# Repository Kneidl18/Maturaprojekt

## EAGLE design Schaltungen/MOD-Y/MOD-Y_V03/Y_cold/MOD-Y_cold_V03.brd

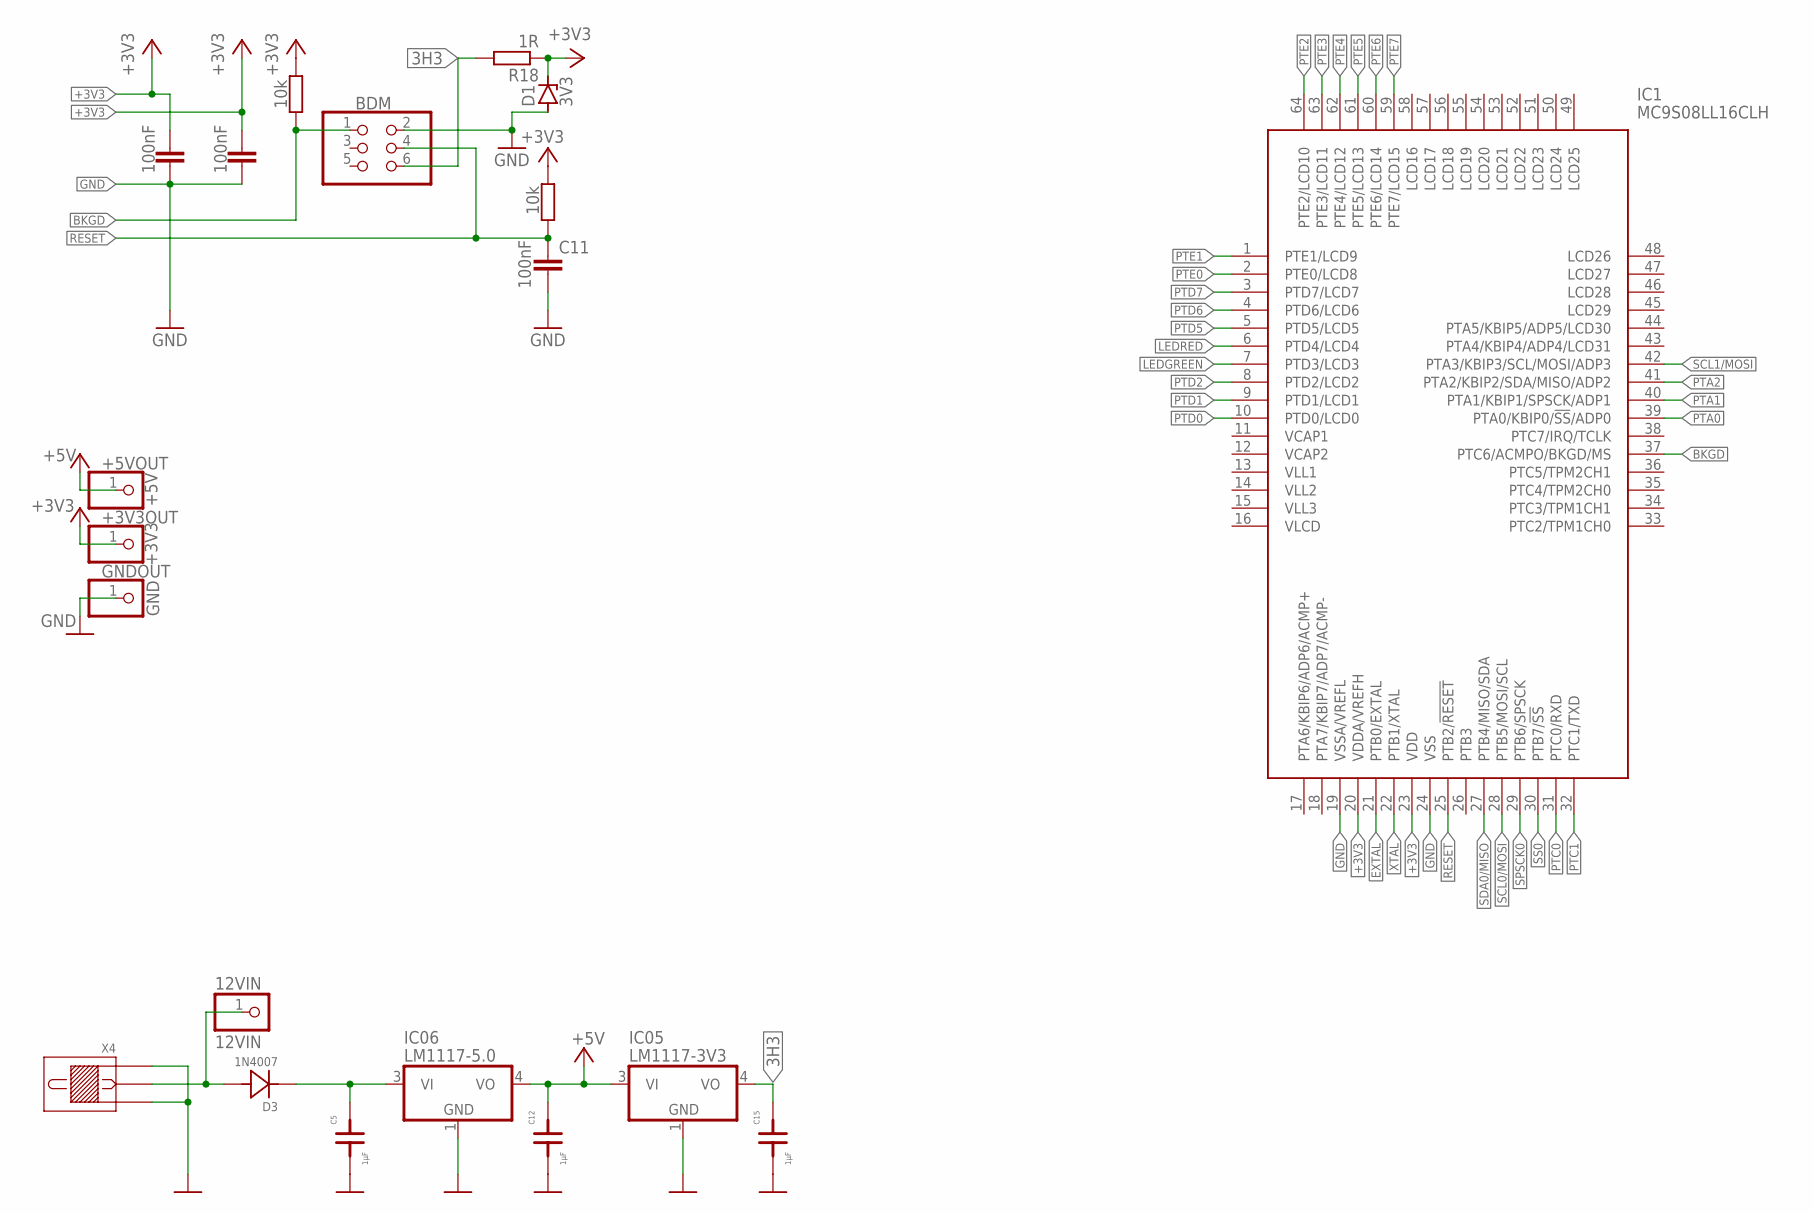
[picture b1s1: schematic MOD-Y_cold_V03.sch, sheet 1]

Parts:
12VIN: 12VIN; 1X01
+3V3OUT: +3V3; 1X01
+5VOUT: +5V; 1X01
BDM: PINHD-2X3; 2X03
C5, C12, C15: 1µF; 0805F
C9, C10, C11: 100nF; C0805
D1: 3V3; SOD80C
D3: 1N4007; MELF_B
GNDOUT: GND; 1X01
IC1: MC9S08LL16CLH; QFP50P1200X1200X160-64N
IC05: LM1117-3V3; DPAK
IC06: LM1117-5.0; DPAK
R16, R17: 10k; R0805
R18: 1R; R0805
X4: SPP

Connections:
3H3: BDM.6, C15.2, IC05.4 (VO), R18.2
+3V3: +3V3OUT.1, C9.1, C10.1, D1.C, IC1.20 (VDDA/VREFH), IC1.23 (VDD), R16.2, R17.2, R18.1; also elsewhere on the board
+5V: +5VOUT.1, C12.2, IC05.3 (VI), IC06.4 (VO); also elsewhere on the board
BKGD: BDM.1, IC1.37 (PTC6/ACMPO/BKGD/MS), R16.1
EXTAL: IC1.21 (PTB0/EXTAL); also elsewhere on the board
GND: BDM.2, C5.1, C9.2, C10.2, C11.2, C12.1, C15.1, D1.A, GNDOUT.1, IC1.19 (VSSA/VREFL), IC1.24 (VSS), IC05.1 (GND), IC06.1 (GND), X4.1, X4.3; also elsewhere on the board
LEDGREEN: IC1.7 (PTD3/LCD3); also elsewhere on the board
LEDRED: IC1.6 (PTD4/LCD4); also elsewhere on the board
unnamed: C5.2, D3.K, IC06.3 (VI)
unnamed: 12VIN.1, D3.A, X4.2
PTA0: IC1.39 (PTA0/KBIP0/!SS!/ADP0); also elsewhere on the board
PTA1: IC1.40 (PTA1/KBIP1/SPSCK/ADP1); also elsewhere on the board
PTA2: IC1.41 (PTA2/KBIP2/SDA/MISO/ADP2); also elsewhere on the board
PTC0: IC1.31 (PTC0/RXD); also elsewhere on the board
PTC1: IC1.32 (PTC1/TXD); also elsewhere on the board
PTD0: IC1.10 (PTD0/LCD0)
PTD1: IC1.9 (PTD1/LCD1)
PTD2: IC1.8 (PTD2/LCD2)
PTD5: IC1.5 (PTD5/LCD5); also elsewhere on the board
PTD6: IC1.4 (PTD6/LCD6); also elsewhere on the board
PTD7: IC1.3 (PTD7/LCD7); also elsewhere on the board
PTE0: IC1.2 (PTE0/LCD8); also elsewhere on the board
PTE1: IC1.1 (PTE1/LCD9); also elsewhere on the board
PTE2: IC1.64 (PTE2/LCD10); also elsewhere on the board
PTE3: IC1.63 (PTE3/LCD11); also elsewhere on the board
PTE4: IC1.62 (PTE4/LCD12); also elsewhere on the board
PTE5: IC1.61 (PTE5/LCD13); also elsewhere on the board
PTE6: IC1.60 (PTE6/LCD14)
PTE7: IC1.59 (PTE7/LCD15)
RESET: BDM.4, C11.1, IC1.25 (PTB2/!RESET), R17.1
SCL0/MOSI: IC1.28 (PTB5/MOSI/SCL); also elsewhere on the board
SCL1/MOSI: IC1.42 (PTA3/KBIP3/SCL/MOSI/ADP3)
SDA0/MISO: IC1.27 (PTB4/MISO/SDA); also elsewhere on the board
SPSCK0: IC1.29 (PTB6/SPSCK); also elsewhere on the board
SS0: IC1.30 (PTB7/!SS); also elsewhere on the board
XTAL: IC1.22 (PTB1/XTAL); also elsewhere on the board

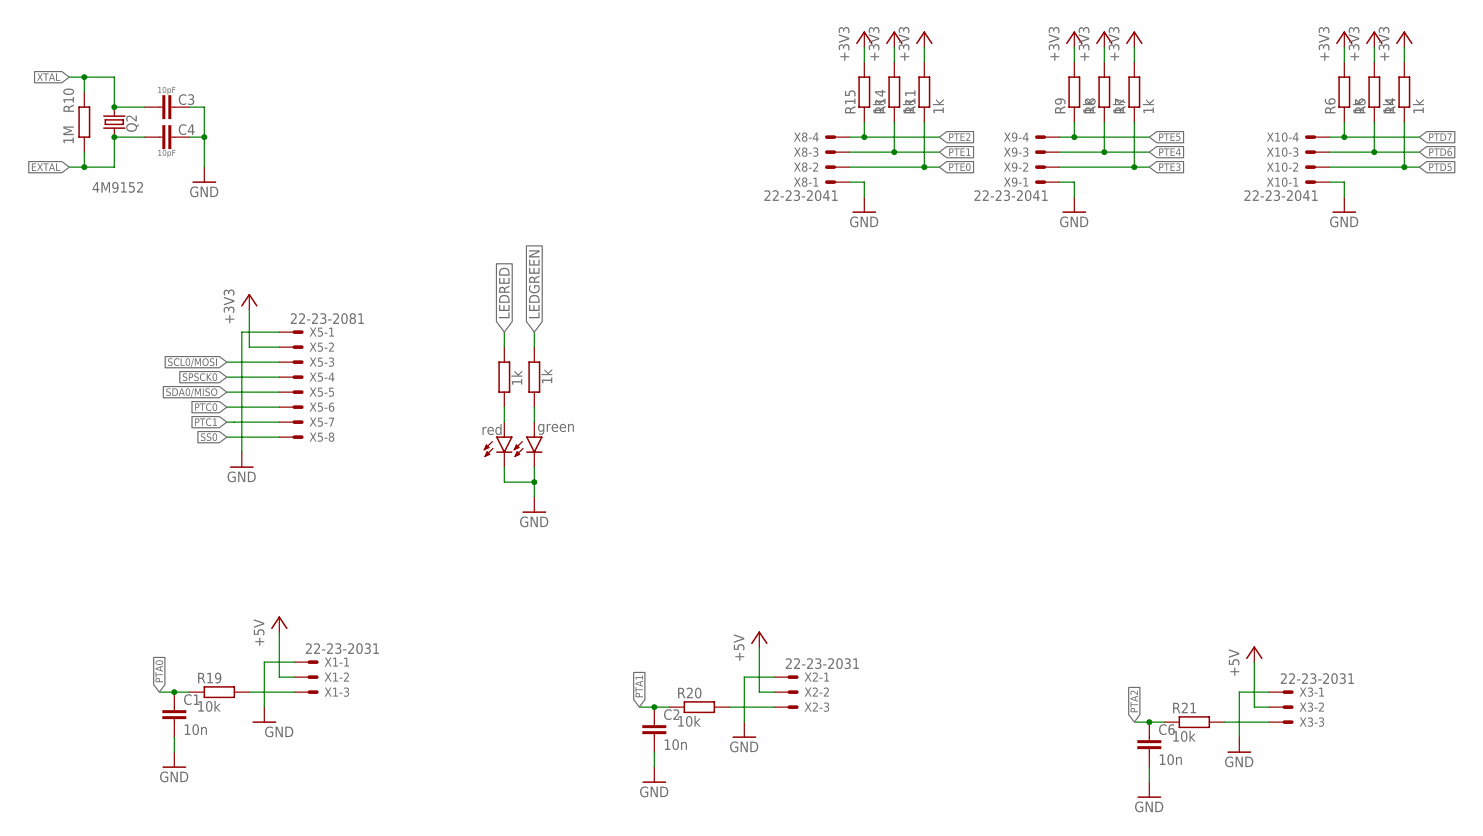
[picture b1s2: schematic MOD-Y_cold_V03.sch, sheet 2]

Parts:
C1, C2, C6: 10n; C0805
C3, C4: 10pF; C0805
LED1: green; CHIP-LED0805
LED2: red; CHIP-LED0805
Q2: 4M9152; HC49UP
R4, R5, R6, R7, R8, R9, R11, R12, R13, R14, R15: 1k; R0805
R10: 1M; R0805
R19, R20, R21: 10k; R0805
X1, X2, X3: 22-23-2031
X5: 22-23-2081
X8, X9, X10: 22-23-2041

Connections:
+3V3: R4.2, R5.2, R6.2, R7.2, R8.2, R9.2, R11.2, R14.2, R15.2, X5.2; also elsewhere on the board
+5V: X1.2, X2.2, X3.2; also elsewhere on the board
EXTAL: C4.1, Q2.1, R10.1; also elsewhere on the board
GND: C1.2, C2.2, C3.2, C4.2, C6.2, LED1.C, LED2.C, X1.1, X2.1, X3.1, X5.1, X8.1, X9.1, X10.1; also elsewhere on the board
LEDGREEN: R13.2; also elsewhere on the board
LEDRED: R12.2; also elsewhere on the board
unnamed: R21.2, X3.3
unnamed: R19.2, X1.3
unnamed: R20.2, X2.3
unnamed: LED2.A, R12.1
unnamed: LED1.A, R13.1
PTA0: C1.1, R19.1; also elsewhere on the board
PTA1: C2.1, R20.1; also elsewhere on the board
PTA2: C6.1, R21.1; also elsewhere on the board
PTC0: X5.6; also elsewhere on the board
PTC1: X5.7; also elsewhere on the board
PTD5: R4.1, X10.2; also elsewhere on the board
PTD6: R5.1, X10.3; also elsewhere on the board
PTD7: R6.1, X10.4; also elsewhere on the board
PTE0: R11.1, X8.2; also elsewhere on the board
PTE1: R14.1, X8.3; also elsewhere on the board
PTE2: R15.1, X8.4; also elsewhere on the board
PTE3: R7.1, X9.2; also elsewhere on the board
PTE4: R8.1, X9.3; also elsewhere on the board
PTE5: R9.1, X9.4; also elsewhere on the board
SCL0/MOSI: X5.3; also elsewhere on the board
SDA0/MISO: X5.5; also elsewhere on the board
SPSCK0: X5.4; also elsewhere on the board
SS0: X5.8; also elsewhere on the board
XTAL: C3.1, Q2.2, R10.2; also elsewhere on the board

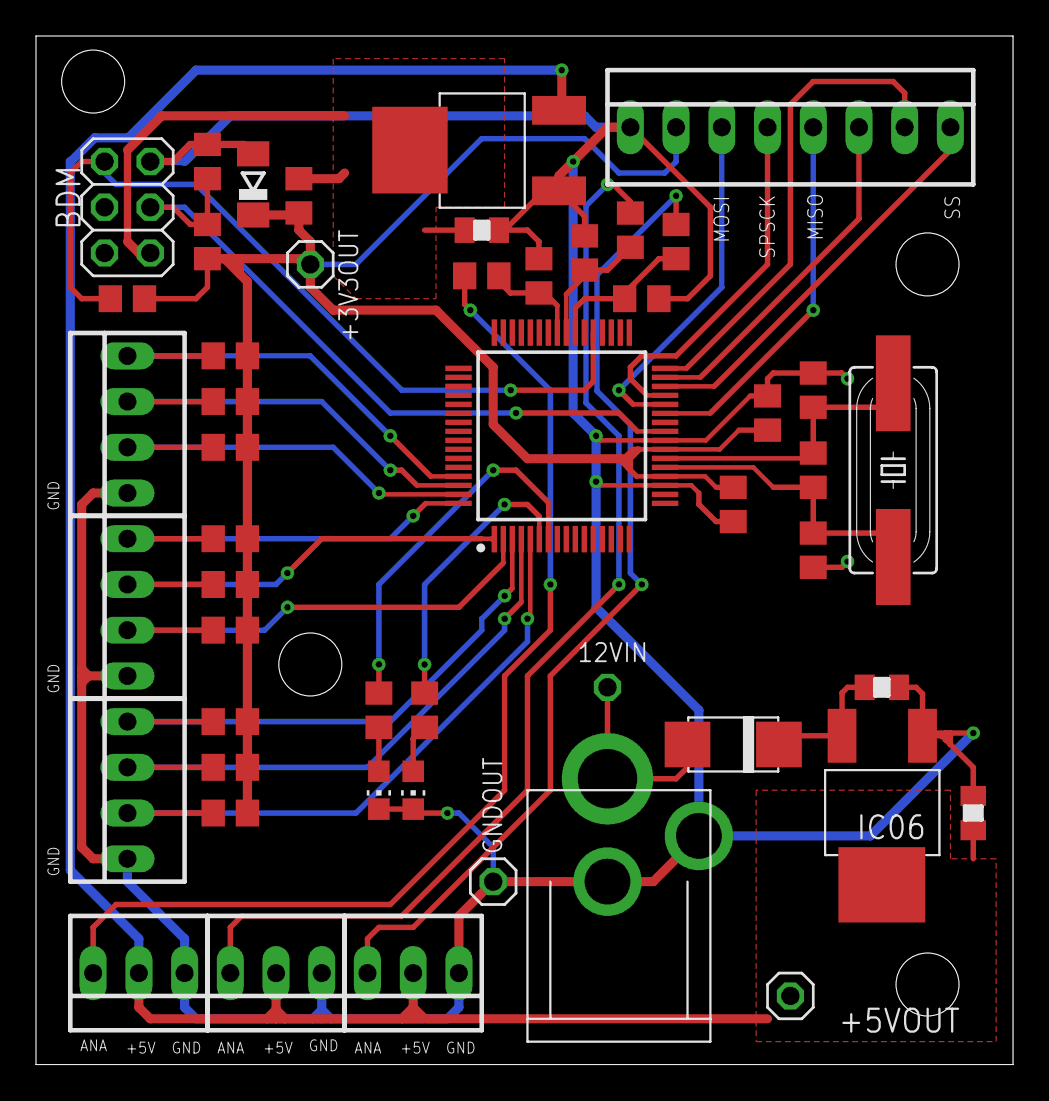
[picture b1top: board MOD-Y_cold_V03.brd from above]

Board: 2 copper layers, 54.3 x 57.1 mm, 50 parts (1 on the bottom side), 35 nets.

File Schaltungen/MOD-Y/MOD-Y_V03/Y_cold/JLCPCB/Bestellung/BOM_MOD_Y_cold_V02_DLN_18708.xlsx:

Comment | Designator | Footprint | LCSC Part #（optional）
10pF | C3, C4 | 0805_C | C1785
1µF | C5, C12, C15 | 0805_C | C28323
10nF | C1, C2, C6 | 0805_C | C1710
100nF | C9, C10, C11 | 0805_C | C49678
1R | R18 | 0805_R | C25271
1k | R4, R5, R6, R7, R8, R9, R11, R12, R13, R14, R15 | 0805_R | C17513
10k | R16, R17, R19, R20, R21 | 0805_R | C17414
1M | R10 | 0805_R | C228604

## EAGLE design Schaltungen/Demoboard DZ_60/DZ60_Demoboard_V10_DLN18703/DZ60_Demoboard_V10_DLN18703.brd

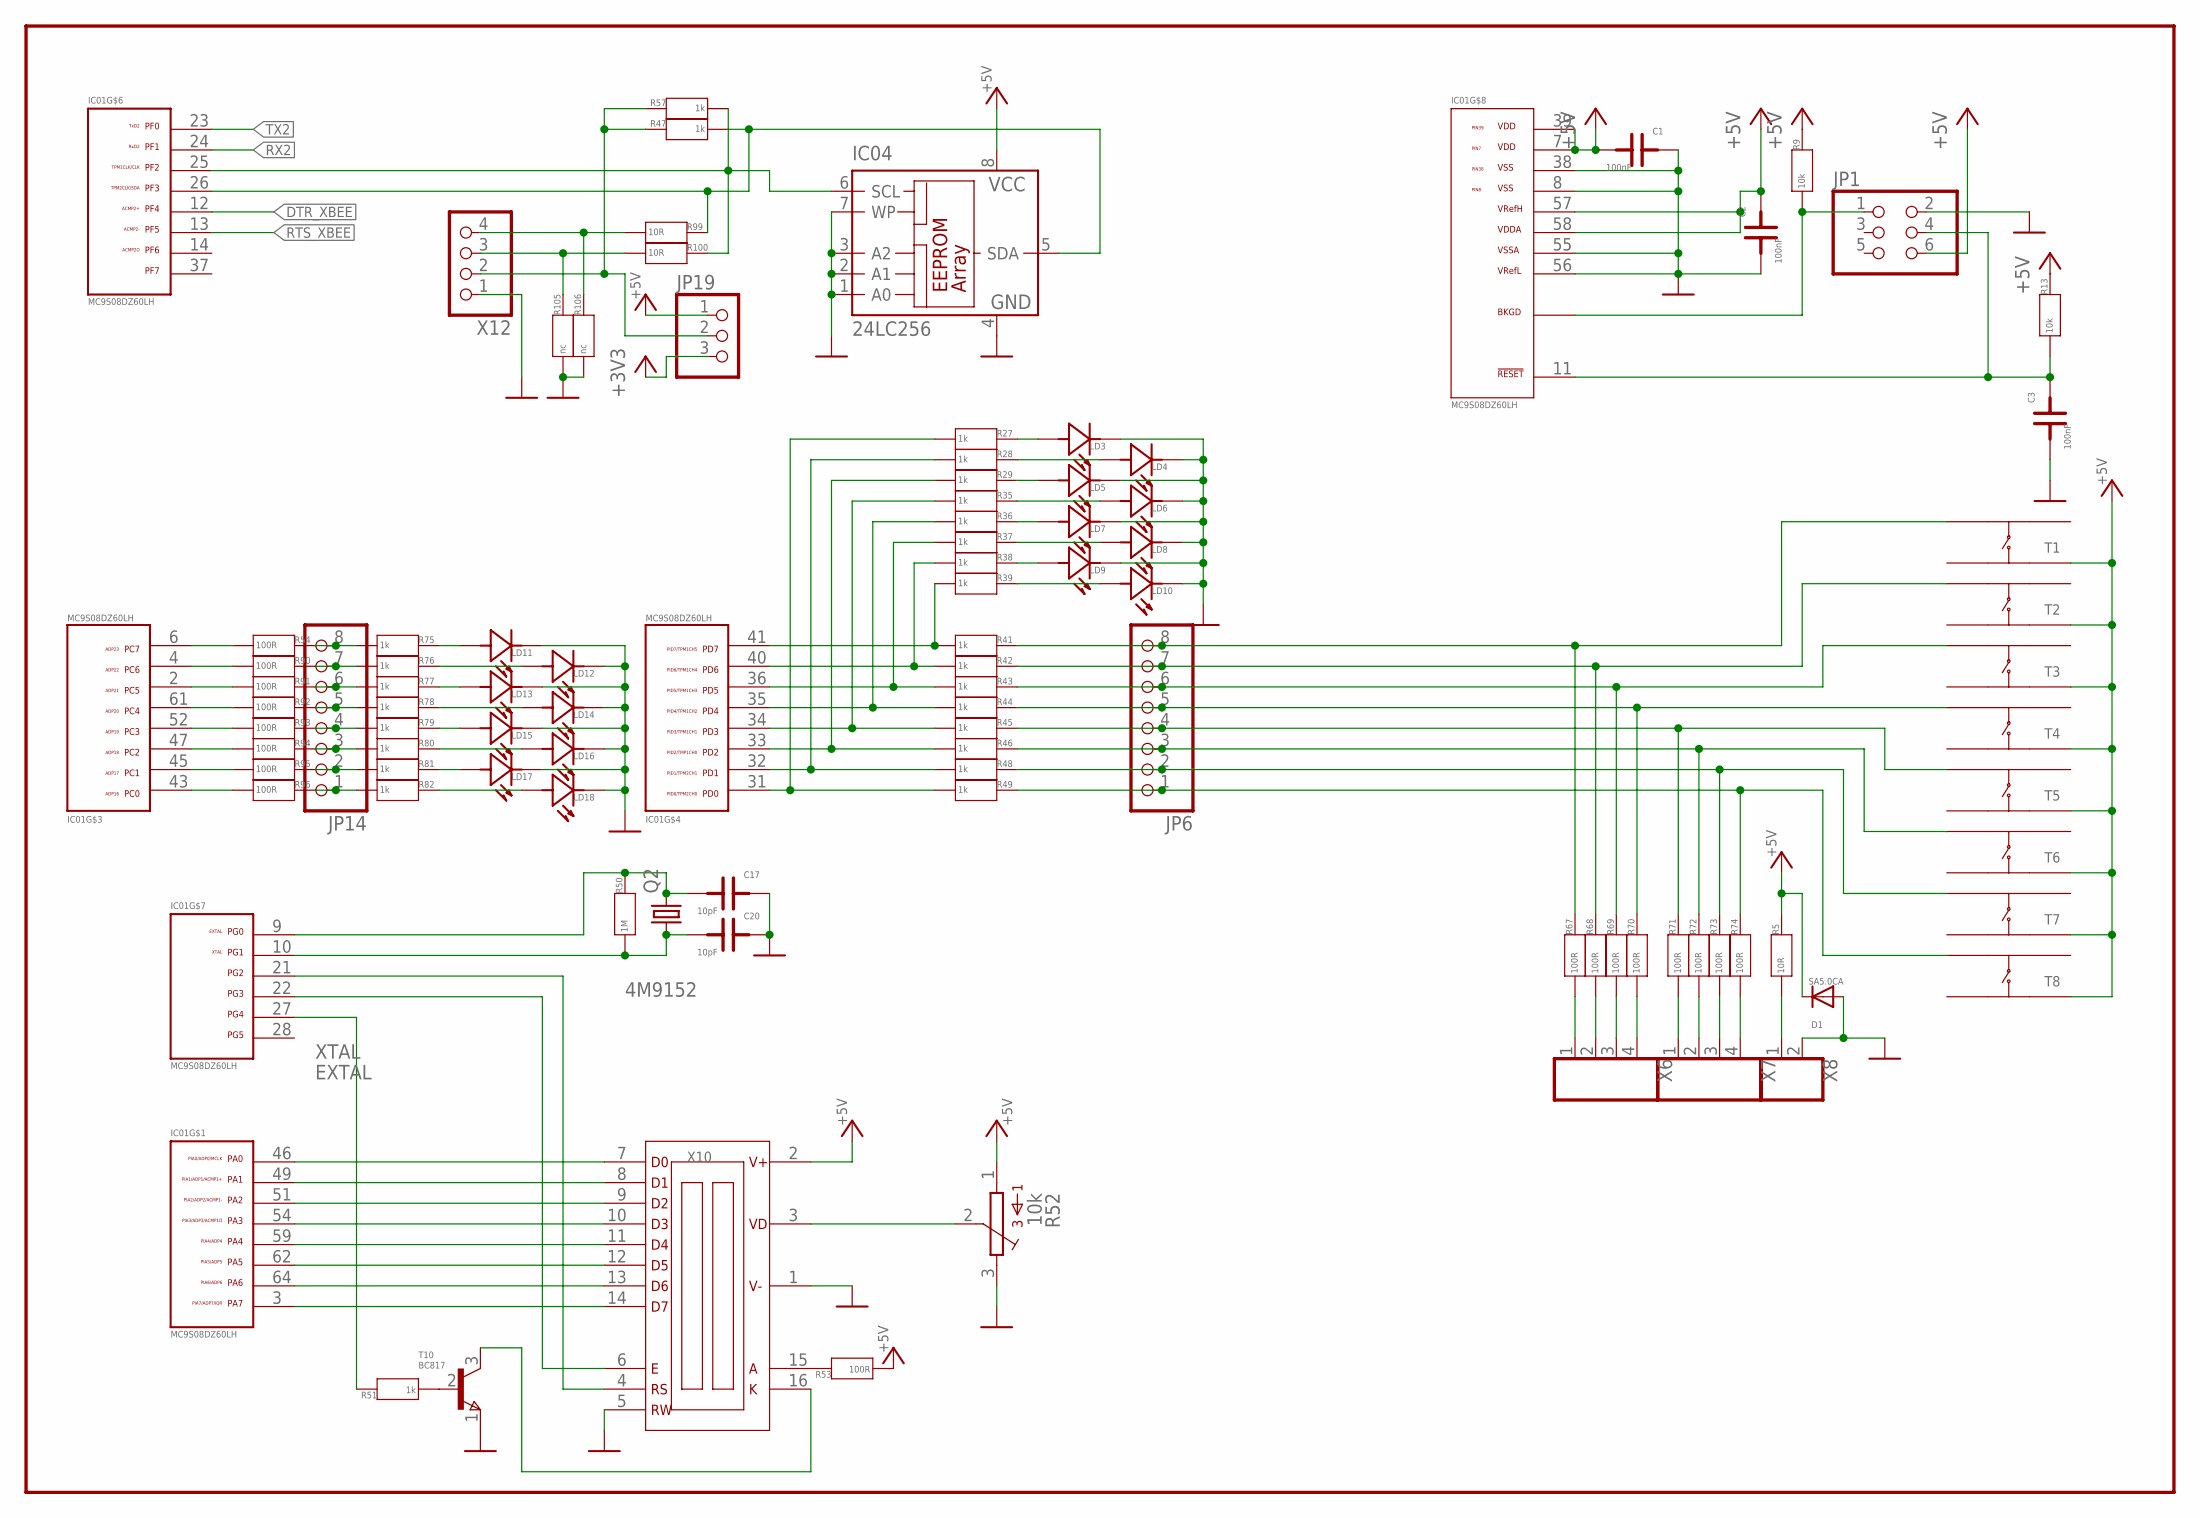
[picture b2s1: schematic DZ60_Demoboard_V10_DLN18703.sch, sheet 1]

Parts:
C1, C2, C3: 100nF; 0805F
C17, C20: 10pF; 0805F
D1: SA5.0CA; SMB
IC01: MC9S08DZ60LH; LQFP64
IC04: 24LC256; SO-08M
JP1: PINHD-2X3; 2X03
JP6, JP14: PINHD-1X8; 1X08
JP19: PINHD-1X3; 1X03
LD3, LD4, LD5, LD6, LD7, LD8, LD9, LD10, LD11, LD12, LD13, LD14, LD15, LD16, LD17, LD18: LEDSMD; 0805LED
Q2: 4M9152; HC49UP
R5, R99, R100: 10R; 0805
R9, R13: 10k; 0805
R27, R28, R29, R35, R36, R37, R38, R39, R41, R42, R43, R44, R45, R46, R47, R48, R49, R51, R57, R75, R76, R77, R78, R79, R80, R81, R82: 1k; 0805
R50: 1M; 0805
R52: 10k; S63X
R53, R54, R67, R68, R69, R70, R71, R72, R73, R74, R90, R91, R92, R93, R94, R95, R96: 100R; 0805
R105, R106: nc; 0805
T1, T2, T3, T4, T5, T6, T7, T8: TASTERTHT; TASTE_THT
T10: BC817; SOT-23
X6, X7: KLEMME4
X8: KLEMME2
X10: FDCC1602G
X12: MX254_4; MX4

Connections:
+3V3: JP19.3; also elsewhere on the board
+5V: C1.1, C2.2, D1.C, IC01.7 (VDD_PIN7), IC01.39 (VDD_PIN39), IC01.57 (VREFH), IC01.58 (VDDA), IC04.8 (VCC), JP1.6, JP19.1, R5.2, R9.2, R13.2, R52.1, R53.1, T1.A1, T2.A1, T3.A1, T4.A1, T5.A1, T6.A1, T7.A1, T8.A1, X10.2 (V+); also elsewhere on the board
BKGD: IC01.42 (BKGD), JP1.1, R9.1
D0: IC01.46 (PA0), X10.7 (D0)
D1: IC01.49 (PA1), X10.8 (D1)
D2: IC01.51 (PA2), X10.9 (D2)
D3: IC01.54 (PA3), X10.10 (D3)
D4: IC01.59 (PA4), X10.11 (D4)
D5: IC01.62 (PA5), X10.12 (D5)
D6: IC01.64 (PA6), X10.13 (D6)
D7: IC01.3 (PA7), X10.14 (D7)
DTR_XBEE: IC01.12 (PF4); also elsewhere on the board
E: IC01.22 (PG3), X10.6 (E)
EXTAL: C20.1, IC01.10 (PG1), Q2.1, R50.1
GND: C1.2, C2.1, C3.1, C17.2, C20.2, D1.A, IC01.8 (VSS_PIN8), IC01.38 (VSS_PIN38), IC01.55 (VSSA), IC01.56 (VREFL), IC04.1 (A0), IC04.2 (A1), IC04.3 (A2), IC04.4 (GND), IC04.7 (WP), JP1.2, LD3.K (1), LD4.K (1), LD5.K (1), LD6.K (1), LD7.K (1), LD8.K (1), LD9.K (1), LD10.K (1), LD11.K (1), LD12.K (1), LD13.K (1), LD14.K (1), LD15.K (1), LD16.K (1), LD17.K (1), LD18.K (1), R52.3, R105.1, R106.1, T10.1 (E), X8.2, X10.1 (V-), X10.5 (RW), X12.1; also elsewhere on the board
LCD_LED1: IC01.27 (PG4), R51.2
unnamed: R53.2, X10.15 (A)
unnamed: LD11.A (2), R75.2
unnamed: LD12.A (2), R76.2
unnamed: LD3.A (2), R27.2
unnamed: LD4.A (2), R28.2
unnamed: LD5.A (2), R29.2
unnamed: LD6.A (2), R35.2
unnamed: LD7.A (2), R36.2
unnamed: LD8.A (2), R37.2
unnamed: LD9.A (2), R38.2
unnamed: LD10.A (2), R39.2
unnamed: R51.1, T10.2 (B)
unnamed: R5.1, X8.1
unnamed: R52.2, X10.3 (VD)
unnamed: T10.3 (C), X10.16 (K)
unnamed: LD13.A (2), R77.2
unnamed: LD14.A (2), R78.2
unnamed: LD15.A (2), R79.2
unnamed: LD16.A (2), R80.2
unnamed: LD17.A (2), R81.2
unnamed: LD18.A (2), R82.2
PC0: JP14.1, R82.1, R96.2
PC0M: IC01.43 (PC0), R96.1
PC1: JP14.2, R81.1, R95.2
PC1M: IC01.45 (PC1), R95.1
PC2: JP14.3, R80.1, R94.2
PC2M: IC01.47 (PC2), R94.1
PC3: JP14.4, R79.1, R93.2
PC3M: IC01.52 (PC3), R93.1
PC4: JP14.5, R78.1, R92.2
PC4M: IC01.61 (PC4), R92.1
PC5: JP14.6, R77.1, R91.2
PC5M: IC01.2 (PC5), R91.1
PC6: JP14.7, R76.1, R90.2
PC6M: IC01.4 (PC6), R90.1
PC7: JP14.8, R54.2, R75.1
PC7M: IC01.6 (PC7), R54.1
PD0: JP6.1, R49.2, R74.2, T8.B2
PD0M: IC01.31 (PD0), R27.1, R49.1
PD1: JP6.2, R48.2, R73.2, T7.B2
PD1M: IC01.32 (PD1), R28.1, R48.1
PD2: JP6.3, R46.2, R72.2, T6.B2
PD2M: IC01.33 (PD2), R29.1, R46.1
PD3: JP6.4, R45.2, R71.2, T5.B2
PD3M: IC01.34 (PD3), R35.1, R45.1
PD4: JP6.5, R44.2, R70.2, T4.B2
PD4M: IC01.35 (PD4), R36.1, R44.1
PD5: JP6.6, R43.2, R69.2, T3.B2
PD5M: IC01.36 (PD5), R37.1, R43.1
PD6: JP6.7, R42.2, R68.2, T2.B2
PD6M: IC01.40 (PD6), R38.1, R42.1
PD7: JP6.8, R41.2, R67.2, T1.B2
PD7M: IC01.41 (PD7), R39.1, R41.1
PF0A: R74.1, X7.4
PF1A: R73.1, X7.3
PF2A: R72.1, X7.2
PF3A: R71.1, X7.1
PF4A: R70.1, X6.4
PF5A: R69.1, X6.3
PF6A: R68.1, X6.2
PF7A: R67.1, X6.1
RESET: C3.2, IC01.11 (RST/), JP1.4, R13.1
RS: IC01.21 (PG2), X10.4 (RS)
RTS_XBEE: IC01.13 (PF5); also elsewhere on the board
RX2: IC01.24 (PF1); also elsewhere on the board
SCL_PF2: IC01.25 (PF2), IC04.6 (SCL), R57.1, R100.2
SCL_PIN: R100.1, R105.2, X12.3
SDA_PF3: IC01.26 (PF3), IC04.5 (SDA), R47.1, R99.2
SDA_PIN: R99.1, R106.2, X12.4
TX2: IC01.23 (PF0); also elsewhere on the board
U_I2C: JP19.2, R47.2, R57.2, X12.2
XTAL: C17.1, IC01.9 (PG0), Q2.2, R50.2

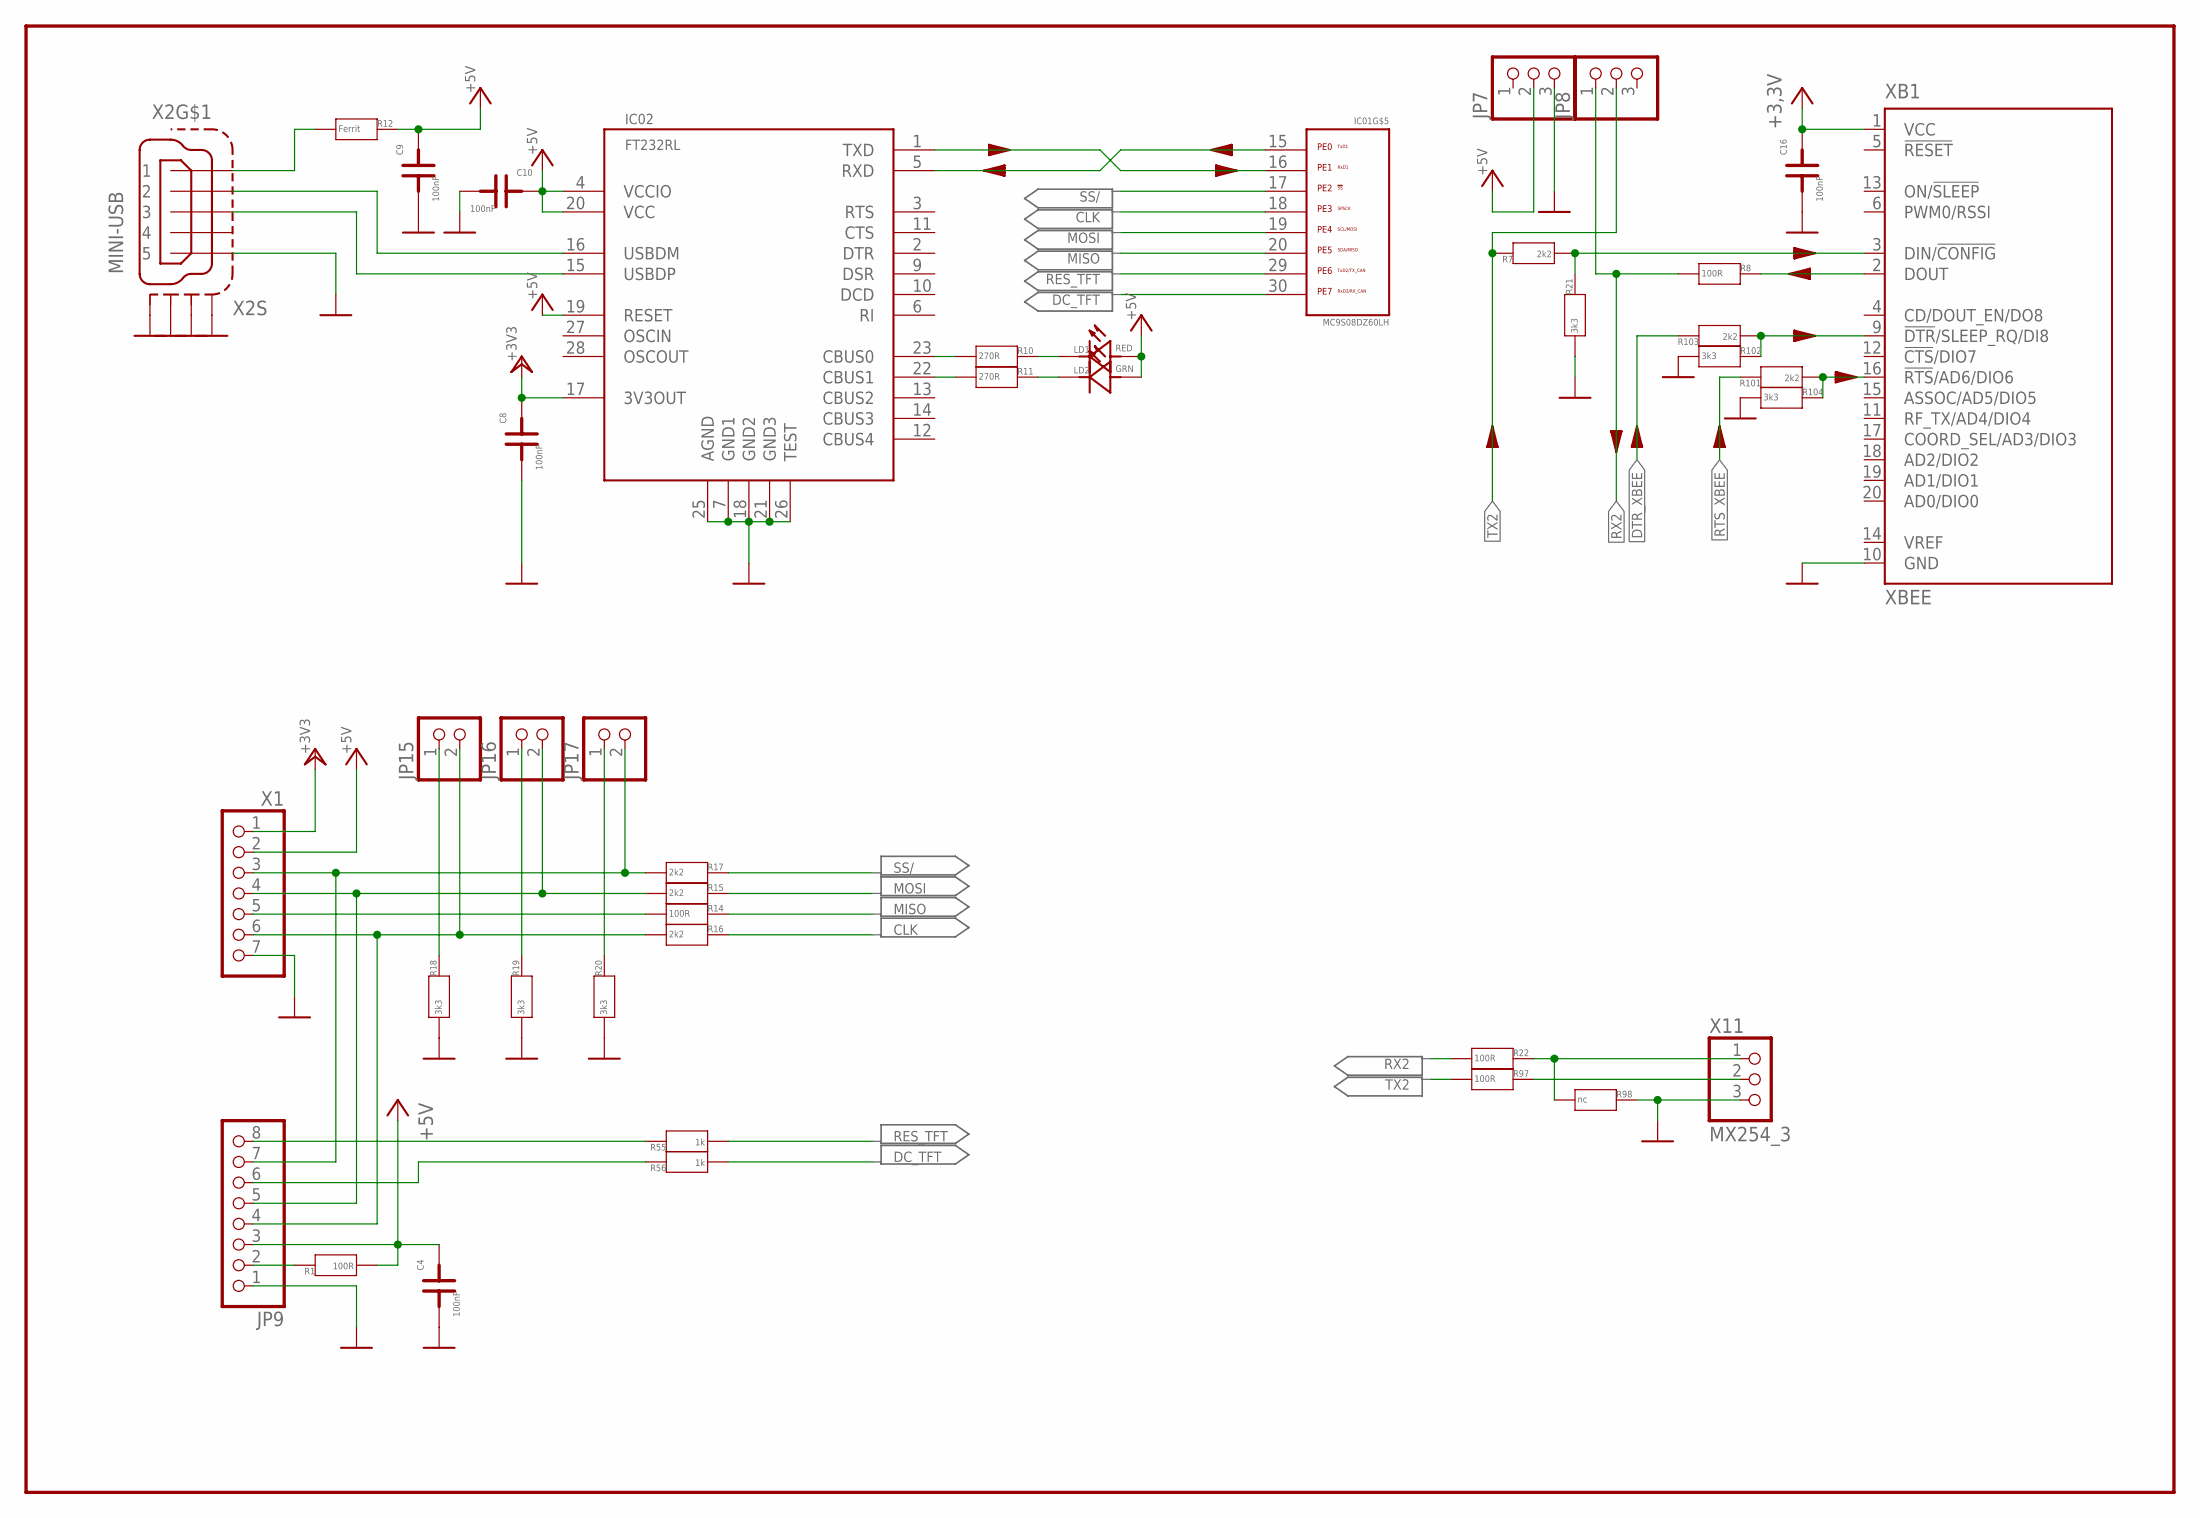
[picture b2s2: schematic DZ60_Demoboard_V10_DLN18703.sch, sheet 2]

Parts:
C4, C8, C9, C10, C16: 100nF; 0805F
IC01: MC9S08DZ60LH; LQFP64
IC02: FT232RL; SSOP28
JP7, JP8: PINHD-1X3; 1X03
JP9: PINHD-1X8; 1X08
JP15, JP16, JP17: PINHD-1X2; 1X02
LD1: RED; 0805LED
LD2: GRN; 0805LED
R1, R8, R14, R22, R97: 100R; 0805
R7, R15, R16, R17, R101, R103: 2k2; 0805
R10, R11: 270R; 0805
R12: Ferrit; 1206
R18, R19, R20, R21, R102, R104: 3k3; 0805
R55, R56: 1k; 0805
R98: nc; 0805
X1: MX254_7; MX7
X2: MINI-USB; 32005-201
X11: MX254_3; MX3
XB1: XBEE

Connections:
+3V3: C8.2, C16.2, IC02.17 (3V3OUT), X1.1, XB1.1 (VCC); also elsewhere on the board
+5V: C4.2, C9.2, C10.2, IC02.4 (VCCIO), IC02.19 (RESET), IC02.20 (VCC), JP7.2, JP9.3, LD1.A (2), LD2.A (2), R1.1, R12.2, X1.2; also elsewhere on the board
CLK: IC01.18 (PE3), R16.2
DC_TFT: IC01.30 (PE7), R56.1
DTR_XBEE: R103.2; also elsewhere on the board
GND: C4.1, C8.1, C9.1, C10.1, C16.1, IC02.7 (GND1), IC02.18 (GND2), IC02.21 (GND3), IC02.25 (AGND), IC02.26 (TEST), JP7.3, JP9.1, R18.1, R19.1, R20.1, R21.1, R98.2, R102.1, R104.1, X1.7, X2.5, X2.M1 (S1), X2.M2 (S2), X2.M3 (S3), X2.M4 (S4), X11.3, XB1.10 (GND); also elsewhere on the board
MISO: IC01.20 (PE5), R14.2
MOSI: IC01.19 (PE4), R15.2
unnamed: LD1.K (1), R10.2
unnamed: R14.1, X1.5
unnamed: IC02.23 (CBUS0), R10.1
unnamed: LD2.K (1), R11.2
unnamed: IC02.22 (CBUS1), R11.1
unnamed: JP9.8, R55.2
unnamed: JP9.2, R1.2
unnamed: JP9.4, JP15.2, R16.1, X1.6
unnamed: JP9.7, JP17.2, R17.1, X1.3
unnamed: JP9.6, R56.2
unnamed: JP17.1, R20.2
unnamed: JP16.1, R19.2
unnamed: JP15.1, R18.2
unnamed: JP9.5, JP16.2, R15.1, X1.4
unnamed: R8.2, XB1.2 (DOUT)
unnamed: R7.1, R21.2, XB1.3 (DIN/!CONFIG)
unnamed: R101.1, R104.2, XB1.16 (!RTS!/AD6/DIO6)
unnamed: R102.2, R103.1, XB1.9 (!DTR!/SLEEP_RQ/DI8)
RES_TFT: IC01.29 (PE6), R55.1
RTS_XBEE: R101.2; also elsewhere on the board
RX1: IC01.16 (PE1), IC02.1 (TXD)
RX2: JP8.1, R8.1, R22.1; also elsewhere on the board
RX2_PINHEAD: R22.2, R98.1, X11.1
SS/: IC01.17 (PE2), R17.2
TX1: IC01.15 (PE0), IC02.5 (RXD)
TX2: JP8.2, R7.2, R97.1; also elsewhere on the board
TX2_PINHEAD: R97.2, X11.2
USB_1: R12.1, X2.1
USB_2: IC02.16 (USBDM), X2.2
USB_3: IC02.15 (USBDP), X2.3

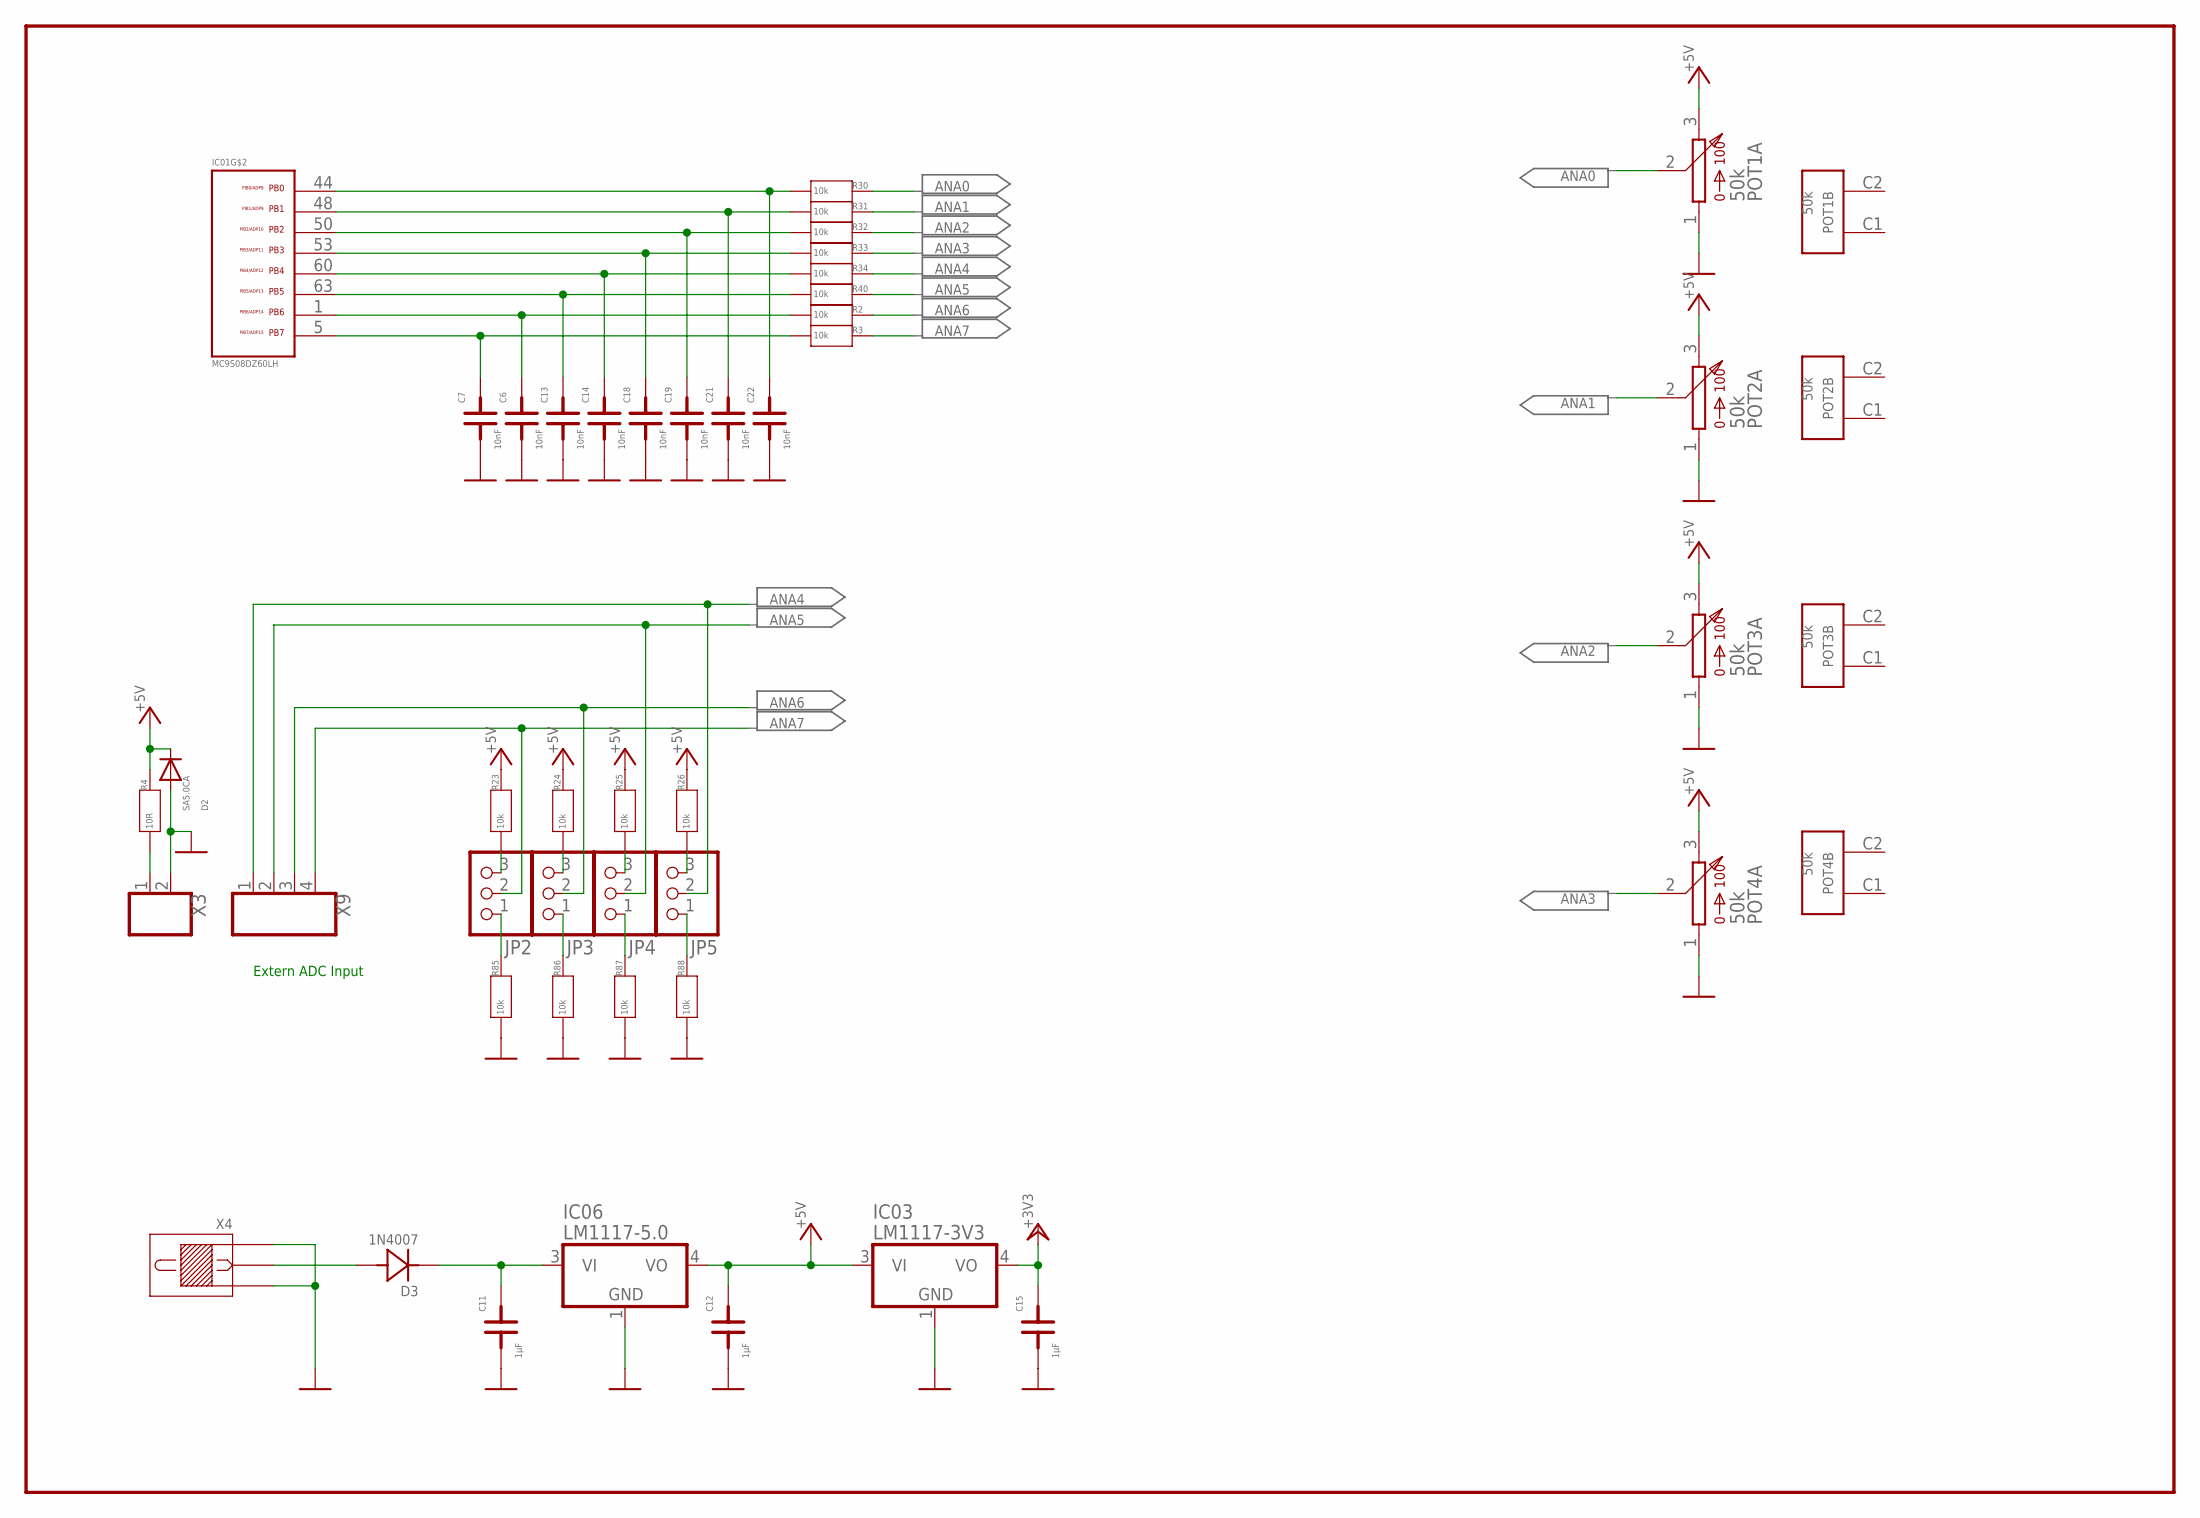
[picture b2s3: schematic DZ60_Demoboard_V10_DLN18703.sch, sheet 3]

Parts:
C6, C7, C13, C14, C18, C19, C21, C22: 10nF; 0805F
C11, C12, C15: 1µF; 0805F
D2: SA5.0CA; SMB
D3: 1N4007; MELF_B
IC01: MC9S08DZ60LH; LQFP64
IC03: LM1117-3V3; DPAK
IC06: LM1117-5.0; DPAK
JP2, JP3, JP4, JP5: PINHD-1X3; 1X03
POT1, POT2, POT3, POT4: 50k; ALPS_VERTICAL
R2, R3, R23, R24, R25, R26, R30, R31, R32, R33, R34, R40, R85, R86, R87, R88: 10k; 0805
R4: 10R; 0805
X3: KLEMME2
X4: SPP
X9: KLEMME4

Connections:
+3V3: C15.2, IC03.4 (VO); also elsewhere on the board
+5V: C12.2, D2.C, IC03.3 (VI), IC06.4 (VO), POT1.3, POT2.3, POT3.3, POT4.3, R4.2, R23.2, R24.2, R25.2, R26.2; also elsewhere on the board
ADCPB0: C22.2, IC01.44 (PB0), R30.1
ADCPB1: C21.2, IC01.48 (PB1), R31.1
ADCPB2: C19.2, IC01.50 (PB2), R32.1
ADCPB3: C18.2, IC01.53 (PB3), R33.1
ADCPB4: C14.2, IC01.60 (PB4), R34.1
ADCPB5: C13.2, IC01.63 (PB5), R40.1
ADCPB6: C6.2, IC01.1 (PB6), R2.1
ADCPB7: C7.2, IC01.5 (PB7), R3.1
ANA0: POT1.2, R30.2
ANA1: POT2.2, R31.2
ANA2: POT3.2, R32.2
ANA3: POT4.2, R33.2
ANA4: JP5.2, R34.2, X9.1
ANA5: JP4.2, R40.2, X9.2
ANA6: JP3.2, R2.2, X9.3
ANA7: JP2.2, R3.2, X9.4
GND: C6.1, C7.1, C11.1, C12.1, C13.1, C14.1, C15.1, C18.1, C19.1, C21.1, C22.1, D2.A, IC03.1 (GND), IC06.1 (GND), POT1.1, POT2.1, POT3.1, POT4.1, R85.1, R86.1, R87.1, R88.1, X3.2, X4.1, X4.3; also elsewhere on the board
unnamed: R4.1, X3.1
unnamed: C11.2, D3.K, IC06.3 (VI)
unnamed: D3.A, X4.2
unnamed: JP5.3, R26.1
unnamed: JP4.3, R25.1
unnamed: JP3.3, R24.1
unnamed: JP2.3, R23.1
unnamed: JP2.1, R85.2
unnamed: JP3.1, R86.2
unnamed: JP4.1, R87.2
unnamed: JP5.1, R88.2

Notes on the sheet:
Extern ADC Input

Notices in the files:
parts and their libraries:
COPYRIGHT: Copyright (C) 2022 Ultra Librarian. All rights reserved.
